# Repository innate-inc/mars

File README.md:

<div align="center">

<!-- Add your banner image here -->
<!--  -->

# Mars - A Personal AI Robot

*Complete design files and documentation for the Mars robot platform*

</div>

---

> [!WARNING]
> **This is an alpha release** - Breaking changes may occur. DIY builds are as-is without warranty.
> Purchase from us for guaranteed upgrades and full support.

---

## Philosophy

At Innate, we believe every builder should be a part of the robotics revolution, just like they were for the Personal Computer revolution.

To do so, two things are required: making robots **affordable**, but also **intuitive** and **powerful** to build with. MARS is our first platform and comes with every compute and sensor required for a general-purpose robot: navigation, manipulation, interaction with the best of AI.

With it, you can run (and build) VLAs, embodied agents, world models, and every other crazy idea you might have, for a BOM <$1k!

## Key Specifications

### Robotic Arm
- **Degrees of Freedom**: 5-DOF manipulator with modular end effector
- **Reach**: 10 inches (254mm) maximum
- **Payload**: 200g at full extension
- **Integrated Camera**: 150° field of view for vision-based manipulation

### Power
- **Battery Life**: ~5 hours with all systems running (navigation, manipulation, compute) using an 8000mAh battery*
  
*Battery delivered by Innate

For complete specifications, visit the [official documentation](https://docs.innate.bot).

## Repository Structure

This repository contains all the hardware design files you need to build a Mars robot:

### 📁 [Printed Parts](printed-parts/)
3D printable components including shells, layers, arm links, head, and mounting hardware. See the [printed-parts README](printed-parts/README.md) for details.

### 📁 [PCBs](pcbs/)
KiCad projects and production files for the head PCB and main development board. See the [pcbs README](pcbs/README.md) for details.

### Robot Models

[URDFs and bundled meshes](models/mars_description/README.md): the fixed-wheel
reference model and an experimental articulated-wheel physics variant, with
MuJoCo validation tests and documented calibration assumptions.

### 📄 Documentation
- **[Bill of Materials](BOM.md)** - Complete parts list with sourcing information
- **[Assembly Guide](assemblies.zip)** - Step-by-step assembly instructions

## Getting Started

1. **Review the [Bill of Materials](BOM.md)** - Source all required components
2. **Order PCBs** - See [pcbs/README.md](pcbs/README.md) for manufacturing instructions  
3. **3D Print Parts** - See [printed-parts/README.md](printed-parts/README.md) for printing guidelines
4. **Assemble** - Follow the instructions in [assemblies.zip](assemblies.zip)

## Contributing

We welcome contributions from the community! Feel free to:
- 🐛 Report bugs and issues
- 💡 Suggest new features and improvements
- 🔧 Submit pull requests
- 📖 Improve documentation

Please join our [Discord community](https://discord.gg/your-invite-link) to discuss your ideas before making major changes.

---

## 📜 License

This project uses dual licensing to cover hardware and software components:

### Hardware License: CERN-OHL-S-2.0

All hardware designs, PCB files, 3D models, and related documentation in this repository are licensed under the **CERN Open Hardware Licence Version 2 - Strongly Reciprocal** (CERN-OHL-S-2.0).

This is a copyleft license that ensures any modifications or derivative works must also be released under the same license, promoting open collaboration while protecting the open-source nature of the hardware.

📄 [View Hardware License](LICENSE-HARDWARE)  
🔗 [Learn more about CERN-OHL-S](https://ohwr.org/cern_ohl_s_v2.txt)

### Software License: GPL v3

The software components for this robot (to be released separately) are licensed under the **GNU General Public License v3.0** (GPL v3).

This ensures that any software modifications or derivative works remain open source and available to the community.

📄 [View Software License](LICENSE-SOFTWARE) *(Software repository coming soon)*  
🔗 [Learn more about GPL v3](https://www.gnu.org/licenses/gpl-3.0.en.html)

---

<div align="center">

**Built with 💙 by Innate in Palo Alto, California**

[Discord](https://discord.gg/your-invite-link) • [Documentation](https://docs.yoursite.com) • [Website](https://yourwebsite.com)

</div>

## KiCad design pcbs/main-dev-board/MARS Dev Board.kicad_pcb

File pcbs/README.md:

# PCBs

KiCad project files and production-ready outputs for all Mars robot circuit boards.

## 📋 Boards

### Head PCB
**Location**: `head-pcb/`

The head PCB controls sensors and actuators in the robot's head assembly.

- **KiCad Project**: [leader.kicad_pro](head-pcb/leader.kicad_pro)
- **Schematic**: [leader.kicad_sch](head-pcb/leader.kicad_sch)
- **PCB Layout**: [leader.kicad_pcb](head-pcb/leader.kicad_pcb)

**Production Files** (`head-pcb/production/`):
- [Gerbers & Drill Files](head-pcb/production/leader.zip)
- [BOM (Bill of Materials)](head-pcb/production/bom.csv)
- [Component Positions](head-pcb/production/positions.csv)
- [Designators Reference](head-pcb/production/designators.csv)
- [IPC Netlist](head-pcb/production/netlist.ipc)

### Main Development Board
**Location**: `main-dev-board/`

The main development board is the brain of the robot, handling computation and motor control."C:\Users\nick\Documents\Innate\mars\pcbs\main-dev-board\MARS%20Dev%20Board.kicad_pro"

- **KiCad Project**: [innate dev pcb.kicad_pro](main-dev-board/MARS%20Dev%20Board.kicad_pro)
- **Schematic**: [innate dev pcb.kicad_sch](main-dev-board/MARS%20Dev%20Board.kicad_sch)
- **PCB Layout**: [innate dev pcb.kicad_pcb](main-dev-board/MARS%20Dev%20Board.kicad_pcb)
- **3D Model**: [innate dev pcb.step](main-dev-board/MARS%20Dev%20Board.step)

**Production Files** (`main-dev-board/production/`):
- [Gerbers & Drill Files](main-dev-board/production/MARS_Dev_Board.zip)
- [BOM (Bill of Materials)](main-dev-board/production/bom.csv)
- [Component Positions](main-dev-board/production/positions.csv)
- [Designators Reference](main-dev-board/production/designators.csv)
- [IPC Netlist](main-dev-board/production/netlist.ipc)

## Design Modifications

To modify the PCB designs:
1. Install [KiCad 7.0+](https://www.kicad.org/)
2. Open the `.kicad_pro` file in KiCad
3. Make your changes to schematic and/or layout
4. Regenerate production files using KiCad's fabrication output tools

## 📐 Fabrication Toolkit

Both boards include `fabrication-toolkit-options.json` for automated production file generation.

## ⚡ Important Notes

- Always verify board revisions match your BOM
- Double-check component orientations before assembly
- Test boards thoroughly before integration
- Refer to the [main BOM](../BOM.md) for complete sourcing information

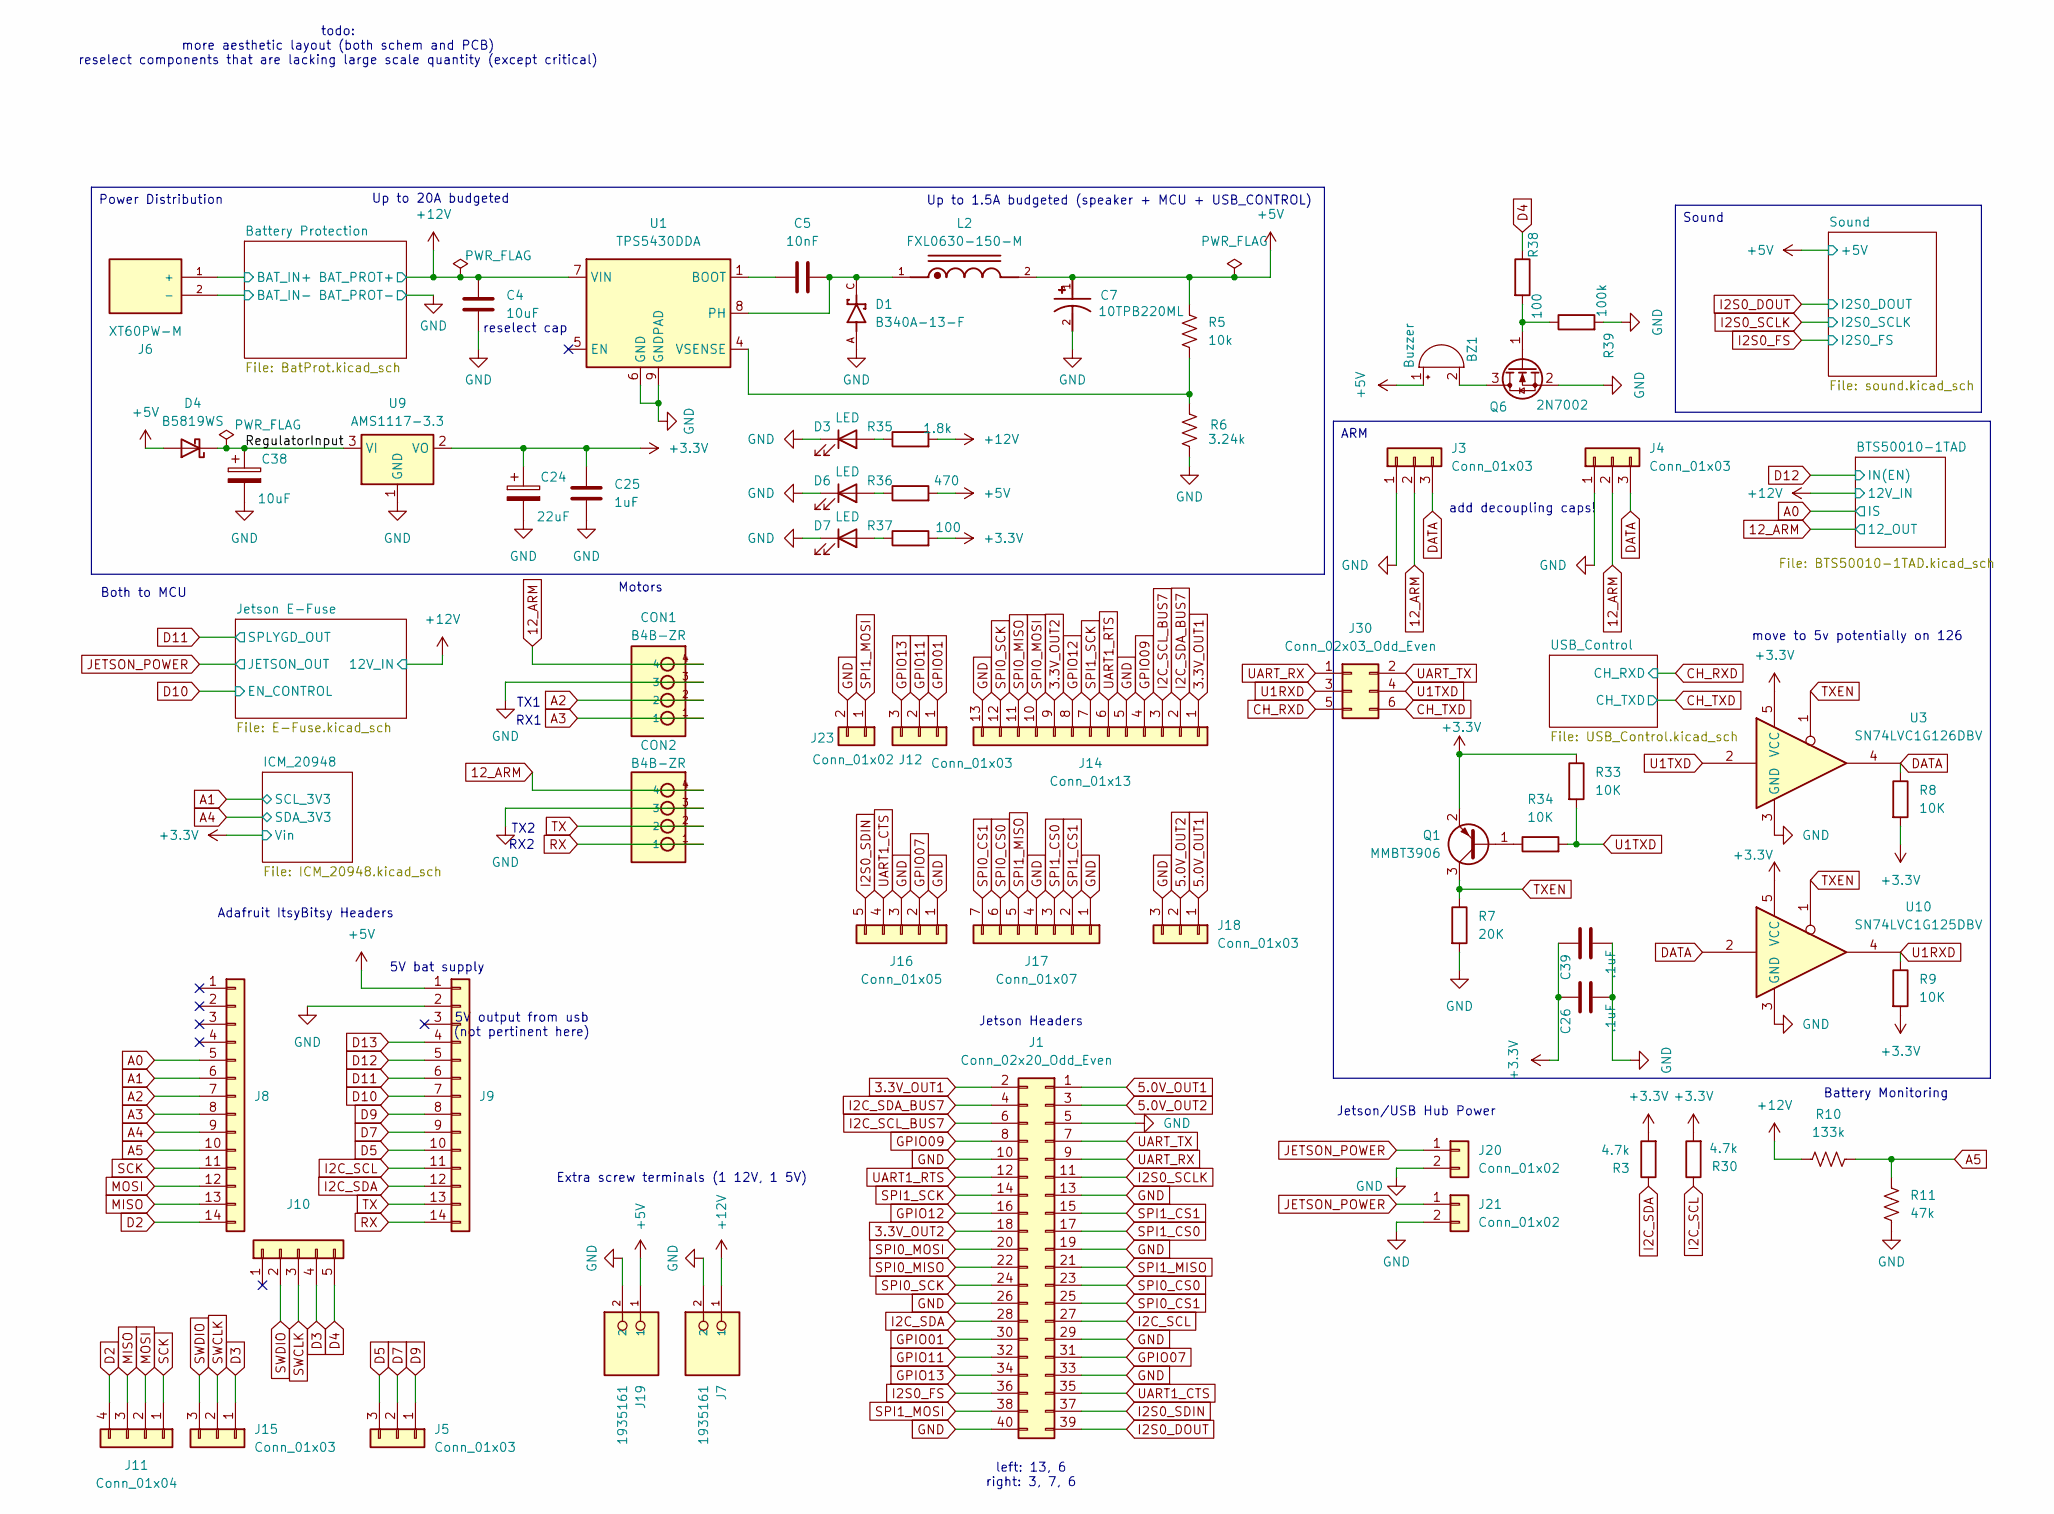
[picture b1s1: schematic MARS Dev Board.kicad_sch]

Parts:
BZ1: Buzzer; XDCR_KXG1205C; LCSC Part # C1122355
C4: 10uF; C_0805_2012Metric; LCSC Part # C3039694
C5: 10nF; C_0603_1608Metric; LCSC Part # C1691
C7: 10TPB220ML; CAP_10TPB220ML; PARTREV 30-Nov-20; LCSC Part # C347545
C24: 22uF; CAPMP3516X190N; LCSC Part # C2158664
C25: 1uF; C_0603_1608Metric; LCSC Part # C29936
C26, C39: .1uF; C_0402_1005Metric; LCSC Part # C56392
C38: 10uF; CAPMP3516X190N; LCSC Part # C7194
CON1, CON2: B4B-ZR; LCSC Part # C157997
D1: B340A-13-F; DIOM5226X240N; PARTREV 17-2; LCSC Part # C908680
D3, D6, D7: LED; D_0603_1608Metric; LCSC Part # C12065
D4: B5819WS; D_SOD-323; LCSC Part # C22624
J1: Conn_02x20_Odd_Even; PinSocket_2x20_P2.54mm_Vertical; LCSC Part # C2682225
J3, J4: Conn_01x03; JST_EH_B3B-EH-A_1x03_P2.50mm_Vertical; LCSC Part # C398546
J5, J12, J15, J18: Conn_01x03; PinSocket_1x03_P2.54mm_Vertical; LCSC Part # C146243
J6: XT60PW-M; AMASS_XT60PW-M; PARTREV V1.2; LCSC Part # C98732
J7, J19: 1935161; TerminalBlock_Phoenix_PT-1,5-2-5.0-H_1x02_P5.00mm_Horizontal; PARTREV 14.12.2022; LCSC Part # C8404
J8, J9: Conn_01x14; PinSocket_1x14_P2.54mm_Vertical; LCSC Part # C18078135
J10, J16: Conn_01x05; PinSocket_1x05_P2.54mm_Vertical; LCSC Part # C18078128
J11: Conn_01x04; PinSocket_1x04_P2.54mm_Vertical; LCSC Part # C7499324
J14: Conn_01x13; PinSocket_1x13_P2.54mm_Vertical; LCSC Part # C2685211
J17: Conn_01x07; PinSocket_1x07_P2.54mm_Vertical; LCSC Part # C18078130
J20, J21: Conn_01x02; JST_VH_B2P-VH_1x02_P3.96mm_Vertical; LCSC Part # C160315
J23: Conn_01x02; PinSocket_1x02_P2.54mm_Vertical; LCSC Part # C18078125
J30: Conn_02x03_Odd_Even; PinHeader_2x03_P2.54mm_Vertical; LCSC Part # C124384
L2: FXL0630-150-M; INDM7066X300N; PARTREV A; LCSC Part # C177243
Q1: MMBT3906; SOT-23; LCSC Part # C53444
Q6: 2N7002; SOT-23; LCSC Part # C8545
R3, R30: 4.7k; R_0402_1005Metric; LCSC Part # C25900
R5: 10k; R_0603_1608Metric; LCSC Part # C15401
R6: 3.24k; R_0603_1608Metric; LCSC Part # C22994
R7: 20K; R_0402_1005Metric; LCSC Part # C25765
R8, R9, R33, R34: 10K; R_0402_1005Metric; LCSC Part # C25744
R10: 133k; R_0402_1005Metric; LCSC Part # C25753
R11: 47k; R_0402_1005Metric; LCSC Part # C25792
R35: 1.8k; R_0402_1005Metric; LCSC Part # C25932
R36: 470; R_0402_1005Metric; LCSC Part # C25167
R37, R38: 100; R_0402_1005Metric; LCSC Part # C25076
R39: 100k; R_0402_1005Metric; LCSC Part # C25741
U1: TPS5430DDA; TI_SO-PowerPAD-8_ThermalVias; LCSC Part # C9864
U3: SN74LVC1G126DBV; SOT-23-5; LCSC Part # C7834
U9: AMS1117-3.3; SOT-223-3_TabPin2; LCSC Part # C347222
U10: SN74LVC1G125DBV; SOT-23-5; LCSC Part # C23654

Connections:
3.3V_OUT1: J1.2, J14.1
3.3V_OUT2: J1.18, J14.9
5.0V_OUT1: J1.1, J18.1
5.0V_OUT2: J1.3, J18.2
12_ARM: CON1.4, CON2.4, J3.2, J4.2; also elsewhere on the board
+3.3V: C24.1, C25.1, C26.1, C39.1, Q1.2 (E), R3.2, R8.2, R9.2, R30.2, R33.1, R37.2, U3.5 (VCC), U9.2 (VO), U10.5 (VCC); also elsewhere on the board
+5V: BZ1.1 (+), C7.1, D4.2 (A), J9.1, J19.1, L2.2, R5.1, R36.2; also elsewhere on the board
+12V: C4.1, J7.1, R10.1, R35.2, U1.7 (VIN); also elsewhere on the board
/Battery Protection/BAT_IN+: J6.1 (+); also elsewhere on the board
/RegulatorInput: C38.1, D4.1 (K), U9.3 (VI)
A0: J8.5; also elsewhere on the board
A1: J8.6; also elsewhere on the board
A2: CON1.2, J8.7
A3: CON1.1, J8.8
A4: J8.9; also elsewhere on the board
A5: J8.10, R10.2, R11.1
CH_RXD: J30.5; also elsewhere on the board
CH_TXD: J30.6; also elsewhere on the board
D2: J8.14, J11.4
D3: J10.4, J15.1
D4: J10.5, R38.1
D5: J5.3, J9.10
D7: J5.2, J9.9
D9: J5.1, J9.8
D10: J9.7; also elsewhere on the board
D11: J9.6; also elsewhere on the board
D12: J9.5; also elsewhere on the board
D13: J9.4
DATA: J3.3, J4.3, R8.1, U3.4, U10.2
GND: C4.2, C7.2, C24.2, C25.2, C26.2, C38.2, C39.2, CON1.3, CON2.3, D1.A, D3.1 (K), D6.1 (K), D7.1 (K), J1.5, J1.10, J1.13, J1.19, J1.26, J1.29, J1.33, J1.40, J3.1, J4.1, J6.2 (-), J7.2, J9.2, J14.5, J14.13, J16.1, J16.3, J17.1, J17.4, J18.3, J19.2, J20.2, J21.2, J23.2, Q6.2 (S), R6.2, R7.2, R11.2, R39.2, U1.6 (GND), U1.9 (GNDPAD), U3.3 (GND), U9.1 (GND), U10.3 (GND); also elsewhere on the board
GPIO01: J1.30, J12.1
GPIO07: J1.31, J16.2
GPIO09: J1.8, J14.4
GPIO11: J1.32, J12.2
GPIO12: J1.16, J14.8
GPIO13: J1.34, J12.3
I2C_SCL: J1.27, J9.11, R30.1
I2C_SCL_BUS7: J1.6, J14.3
I2C_SDA: J1.28, J9.12, R3.1
I2C_SDA_BUS7: J1.4, J14.2
I2S0_DOUT: J1.39; also elsewhere on the board
I2S0_FS: J1.36; also elsewhere on the board
I2S0_SCLK: J1.11; also elsewhere on the board
I2S0_SDIN: J1.37, J16.5
JETSON_POWER: J20.1, J21.1; also elsewhere on the board
MISO: J8.13, J11.3
MOSI: J8.12, J11.2
unnamed: BZ1.2 (-), Q6.3 (D)
unnamed: D3.2 (A), R35.1
unnamed: D6.2 (A), R36.1
unnamed: D7.2 (A), R37.1
unnamed: Q1.1 (B), R34.1
unnamed: Q6.1 (G), R38.2, R39.1
unnamed: C5.1, U1.1 (BOOT)
unnamed: C5.2, D1.C, L2.1, U1.8 (PH)
unnamed: R5.2, R6.1, U1.4 (VSENSE)
RX: CON2.1, J9.14
SCK: J8.11, J11.1
SPI0_CS0: J1.23, J17.6
SPI0_CS1: J1.25, J17.7
SPI0_MISO: J1.22, J14.11
SPI0_MOSI: J1.20, J14.10
SPI0_SCK: J1.24, J14.12
SPI1_CS0: J1.17, J17.3
SPI1_CS1: J1.15, J17.2
SPI1_MISO: J1.21, J17.5
SPI1_MOSI: J1.38, J23.1
SPI1_SCK: J1.14, J14.7
SWCLK: J10.3, J15.2
SWDIO: J10.2, J15.3
TX: CON2.2, J9.13
TXEN: Q1.3 (C), R7.1, U3.1, U10.1
U1RXD: J30.3, R9.1, U10.4
U1TXD: J30.4, R33.2, R34.2, U3.2
UART1_CTS: J1.35, J16.4
UART1_RTS: J1.12, J14.6
UART_RX: J1.9, J30.1
UART_TX: J1.7, J30.2

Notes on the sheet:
Adafruit ItsyBitsy Headers
Battery Monitoring
Up to 20A budgeted
Both to MCU
5V output from usb (not pertinent here)
Extra screw terminals (1 12V, 1 5V)
Jetson/USB Hub Power
RX2
5V bat supply
TX1
add decoupling caps!
Jetson Headers
left: 13, 6 right: 3, 7, 6
TX2
reselect cap
RX1
Motors
move to 5v potentially on 126
Up to 1.5A budgeted (speaker + MCU + USB_CONTROL)
todo: more aesthetic layout (both schem and PCB) reselect components that are lacking large scale quantity (except critical)
Power Distribution
Sound
ARM

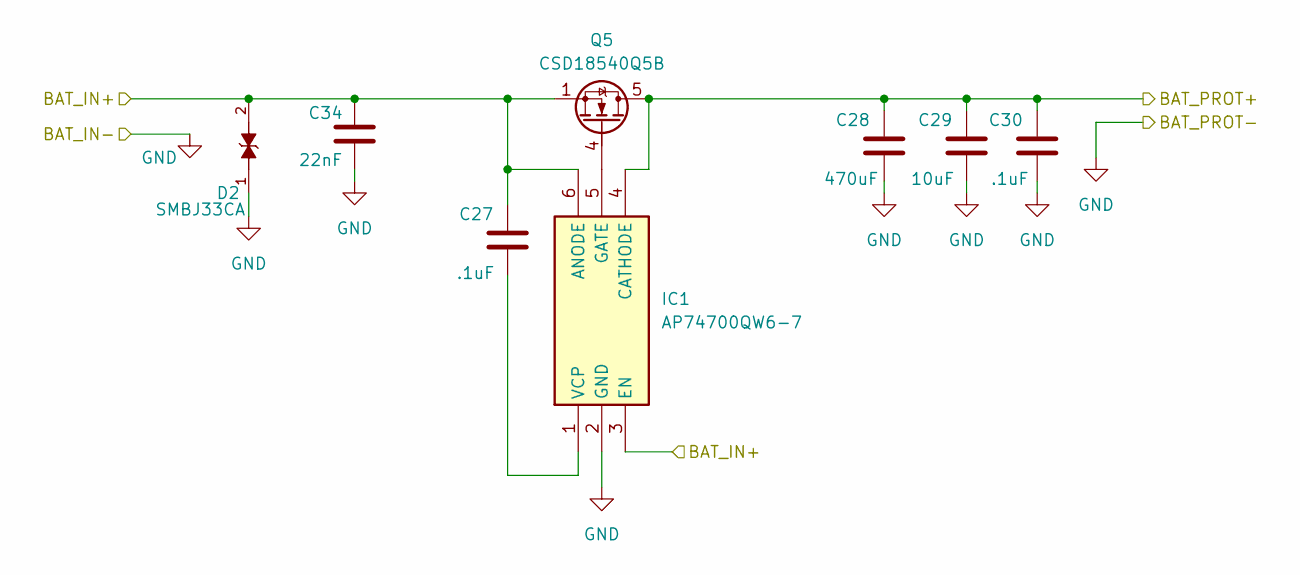
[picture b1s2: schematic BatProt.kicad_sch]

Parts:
C27, C30: .1uF; C_0402_1005Metric; LCSC Part # C56392
C28: 470uF; C_Elec_10x10.2; LCSC Part # C242138
C29: 10uF; C_0805_2012Metric; LCSC Part # C3039694
C34: 22nF; C_0402_1005Metric; LCSC Part # C76703
D2: SMBJ33CA; DIOM4336X265N; PARTREV I2102; LCSC Part # C78420
IC1: AP74700QW6-7; SOT95P280X145-6N; Manufacturer_Part_Number AP74700QW6-7; Mouser Part Number 621-AP74700QW6-7
Q5: CSD18540Q5B; TDSON-8-1; LCSC Part # C86513

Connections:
+12V: C28.1, C29.1, C30.1, IC1.4 (CATHODE), Q5.5 (D); also elsewhere on the board
/Battery Protection/BAT_IN+: C27.1, C34.1, D2.2, IC1.3 (EN), IC1.6 (ANODE), Q5.1 (S), Q5.2 (S), Q5.3 (S); also elsewhere on the board
GND: C28.2, C29.2, C30.2, C34.2, D2.1, IC1.2 (GND); also elsewhere on the board
unnamed: IC1.5 (GATE), Q5.4 (G)
unnamed: C27.2, IC1.1 (VCP)

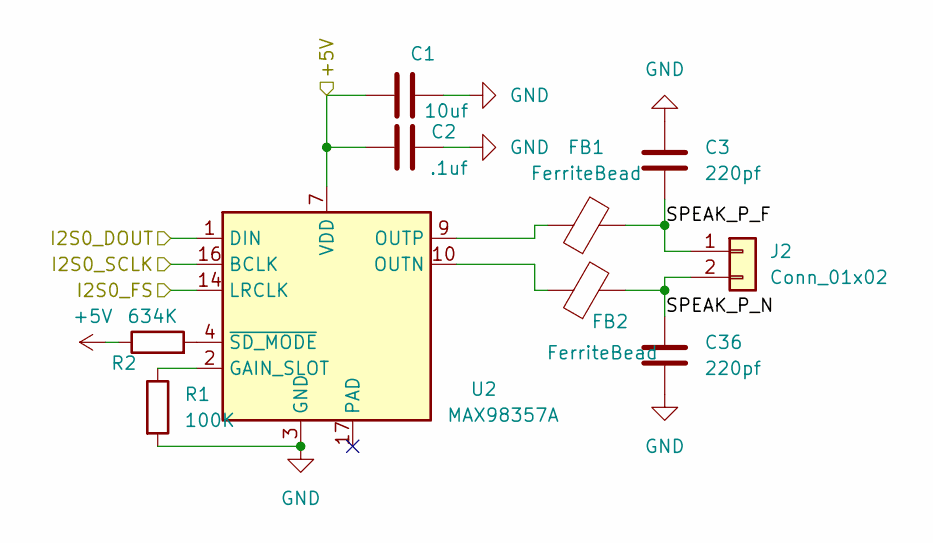
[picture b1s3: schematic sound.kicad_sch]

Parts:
C1: 10uf; C_0603_1608Metric; LCSC Part # C19702
C2: .1uf; C_0402_1005Metric; LCSC Part # C56392
C3, C36: 220pf; C_0402_1005Metric; LCSC Part # C117751
FB1, FB2: FerriteBead; C_0402_1005Metric_Pad0.74x0.62mm_HandSolder; LCSC Part # C85817
J2: Conn_01x02; JST_XH_B2B-XH-A_1x02_P2.50mm_Vertical; LCSC Part # C158012
R1: 100K; R_0402_1005Metric; LCSC Part # C25741
R2: 634K; R_0402_1005Metric; LCSC Part # C270588
U2: MAX98357A; TQFN-16-1EP_3x3mm_P0.5mm_EP1.23x1.23mm; LCSC Part # C910544

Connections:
+5V: C1.1, C2.1, R2.1, U2.7 (VDD), U2.8 (VDD); also elsewhere on the board
/Sound/SPEAK_P_F: C3.2, FB1.2, J2.1
/Sound/SPEAK_P_N: C36.1, FB2.2, J2.2
GND: C1.2, C2.2, C3.1, C36.2, R1.2, U2.3 (GND), U2.11 (GND), U2.15 (GND); also elsewhere on the board
I2S0_DOUT: U2.1 (DIN); also elsewhere on the board
I2S0_FS: U2.14 (LRCLK); also elsewhere on the board
I2S0_SCLK: U2.16 (BCLK); also elsewhere on the board
unnamed: R1.1, U2.2 (GAIN_SLOT)
unnamed: FB2.1, U2.10 (OUTN)
unnamed: FB1.1, U2.9 (OUTP)
unnamed: R2.2, U2.4 (~SD_MODE)

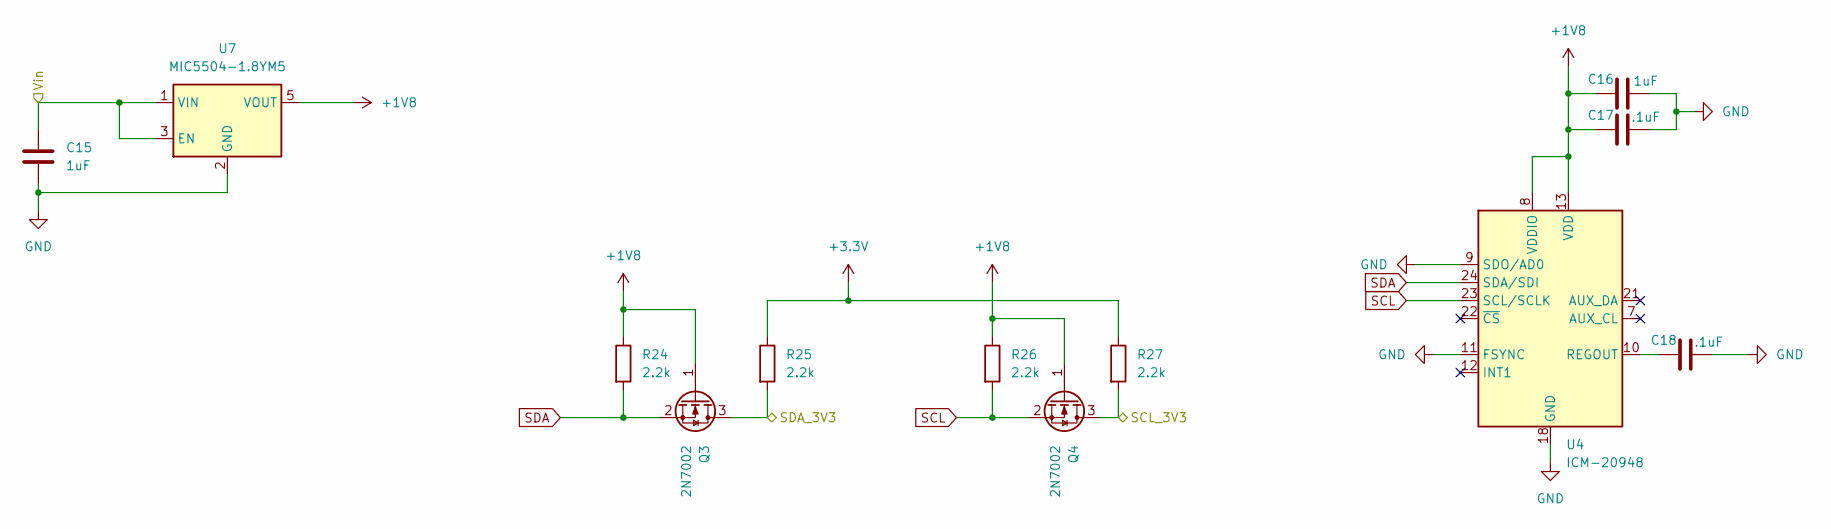
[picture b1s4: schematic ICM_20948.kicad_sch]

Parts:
C15, C16: 1uF; C_0603_1608Metric; LCSC Part # C29936
C17, C18: .1uF; C_0402_1005Metric; LCSC Part # C56392
Q3, Q4: 2N7002; SOT-23; LCSC Part # C8545
R24, R25, R26, R27: 2.2k; R_0402_1005Metric; LCSC Part # C25879
U4: ICM-20948; InvenSense_QFN-24_3x3mm_P0.4mm; LCSC Part # C726001
U7: MIC5504-1.8YM5; SOT-23-5; LCSC Part # C3040643

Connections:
+1V8: C16.1, C17.1, Q3.1 (G), Q4.1 (G), R24.1, R26.1, U4.8 (VDDIO), U4.13 (VDD), U7.5 (VOUT)
+3.3V: C15.1, R25.1, R27.1, U7.1 (VIN), U7.3 (EN); also elsewhere on the board
A1: Q4.3 (D), R27.2; also elsewhere on the board
A4: Q3.3 (D), R25.2; also elsewhere on the board
GND: C15.2, C16.2, C17.2, C18.2, U4.9 (SDO/AD0), U4.11 (FSYNC), U4.18 (GND), U4.20 (GND), U7.2 (GND); also elsewhere on the board
unnamed: C18.1, U4.10 (REGOUT)
SCL: Q4.2 (S), R26.2, U4.23 (SCL/SCLK)
SDA: Q3.2 (S), R24.2, U4.24 (SDA/SDI)

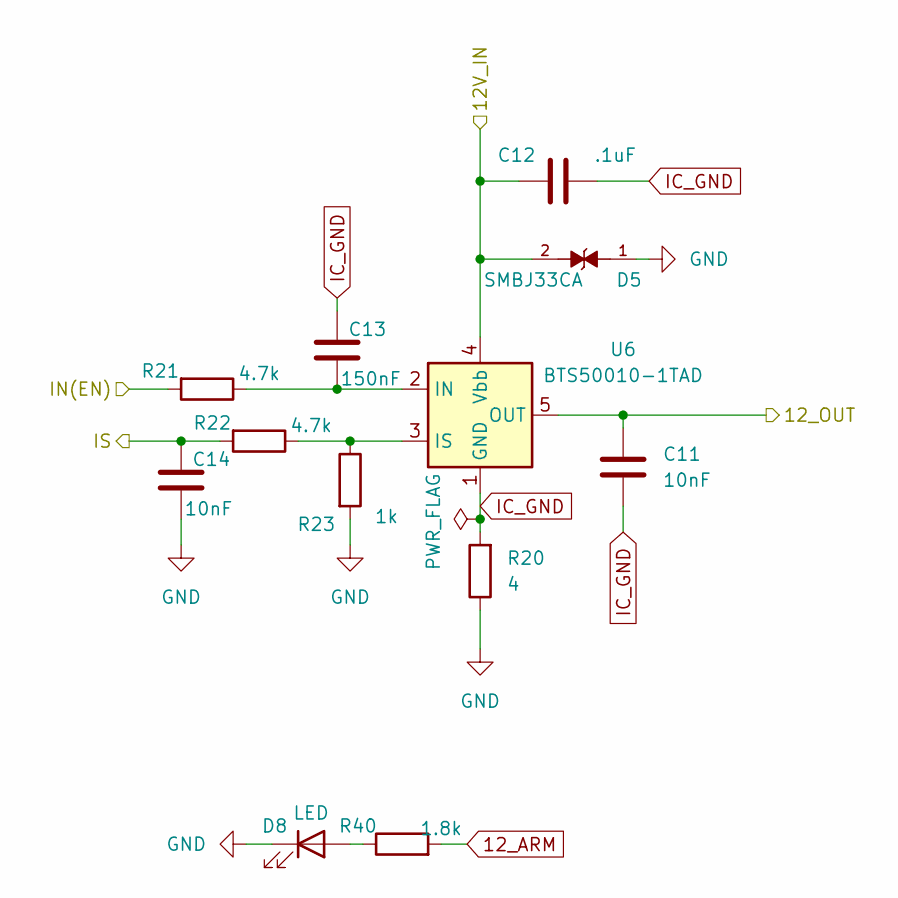
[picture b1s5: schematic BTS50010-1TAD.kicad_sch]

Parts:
C11, C14: 10nF; C_0402_1005Metric; LCSC Part # C76702
C12: .1uF; C_0402_1005Metric; LCSC Part # C56392
C13: 150nF; C_0402_1005Metric; LCSC Part # C5448879
D5: SMBJ33CA; DIOM4336X265N; PARTREV I2102; LCSC Part # C78420
D8: LED; D_0603_1608Metric; LCSC Part # C12065
R20: 4; R_0402_1005Metric; LCSC Part # C270603
R21, R22: 4.7k; R_0402_1005Metric; LCSC Part # C25900
R23: 1k; R_0402_1005Metric; LCSC Part # C11702
R40: 1.8k; R_0402_1005Metric; LCSC Part # C25932
U6: BTS50010-1TAD; TO-263-7_TabPin4; LCSC Part # C2150443

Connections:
12_ARM: C11.1, R40.2, U6.5 (OUT), U6.6 (OUT), U6.7 (OUT); also elsewhere on the board
+12V: C12.1, D5.2, U6.4 (Vbb); also elsewhere on the board
A0: C14.1, R22.2; also elsewhere on the board
D12: R21.2; also elsewhere on the board
GND: C14.2, D5.1, D8.1 (K), R20.1, R23.2; also elsewhere on the board
IC_GND: C11.2, C12.2, C13.1, R20.2, U6.1 (GND)
unnamed: D8.2 (A), R40.1
unnamed: C13.2, R21.1, U6.2 (IN)
unnamed: R22.1, R23.1, U6.3 (IS)

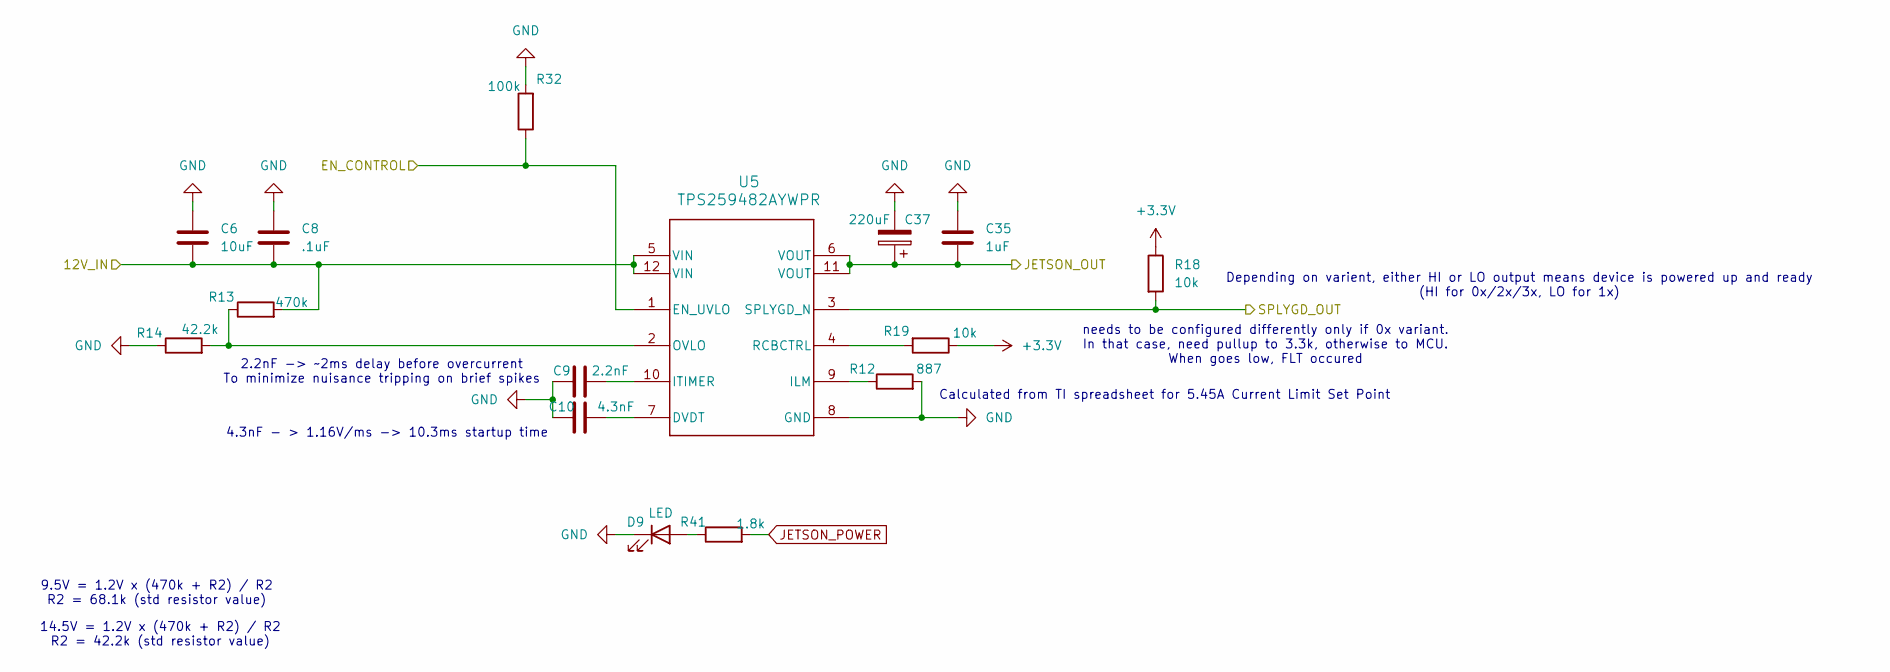
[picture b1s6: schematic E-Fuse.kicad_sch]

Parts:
C6: 10uF; C_0805_2012Metric; LCSC Part # C3039694
C8: .1uF; C_0402_1005Metric; LCSC Part # C56392
C9: 2.2nF; C_0402_1005Metric; LCSC Part # C541386
C10: 4.3nF; C_0402_1005Metric; LCSC Part # C181747
C35: 1uF; C_0603_1608Metric; LCSC Part # C29936
C37: 220uF; C_Elec_8x10.2; LCSC Part # C341198
D9: LED; D_0603_1608Metric; LCSC Part # C12065
R12: 887; R_0402_1005Metric; LCSC Part # C474137
R13: 470k; R_0402_1005Metric; LCSC Part # C25790
R14: 42.2k; R_0402_1005Metric; LCSC Part # C26979
R18, R19: 10k; R_0402_1005Metric; LCSC Part # C25744
R32: 100k; R_0402_1005Metric; LCSC Part # C25741
R41: 1.8k; R_0402_1005Metric; LCSC Part # C25932
U5: TPS259482AYWPR; YWP0012A-MFG; LCSC Part # C22422005

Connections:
+3.3V: R18.1, R19.1; also elsewhere on the board
+12V: C6.2, C8.2, R13.2, U5.5 (VIN), U5.12 (VIN); also elsewhere on the board
D10: R32.1, U5.1 (EN_UVLO); also elsewhere on the board
D11: R18.2, U5.3 (SPLYGD_N); also elsewhere on the board
GND: C6.1, C8.1, C9.1, C10.1, C35.1, C37.2, D9.1 (K), R12.2, R14.1, R32.2, U5.8 (GND); also elsewhere on the board
JETSON_POWER: C35.2, C37.1, R41.2, U5.6 (VOUT), U5.11 (VOUT); also elsewhere on the board
unnamed: D9.2 (A), R41.1
unnamed: C10.2, U5.7 (DVDT)
unnamed: R12.1, U5.9 (ILM)
unnamed: C9.2, U5.10 (ITIMER)
unnamed: R13.1, R14.2, U5.2 (OVLO)
unnamed: R19.2, U5.4 (RCBCTRL)

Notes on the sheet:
14.5V = 1.2V x (470k + R2) / R2 R2 = 42.2k (std resistor value)
Calculated from TI spreadsheet for 5.45A Current Limit Set Point
Depending on varient, either HI or LO output means device is powered up and ready (HI for 0x/2x/3x, LO for 1x)
2.2nF -> ~2ms delay before overcurrent To minimize nuisance tripping on brief spikes
9.5V = 1.2V x (470k + R2) / R2 R2 = 68.1k (std resistor value)
4.3nF - > 1.16V/ms -> 10.3ms startup time
needs to be configured differently only if 0x variant. In that case, need pullup to 3.3k, otherwise to MCU. When goes low, FLT occured

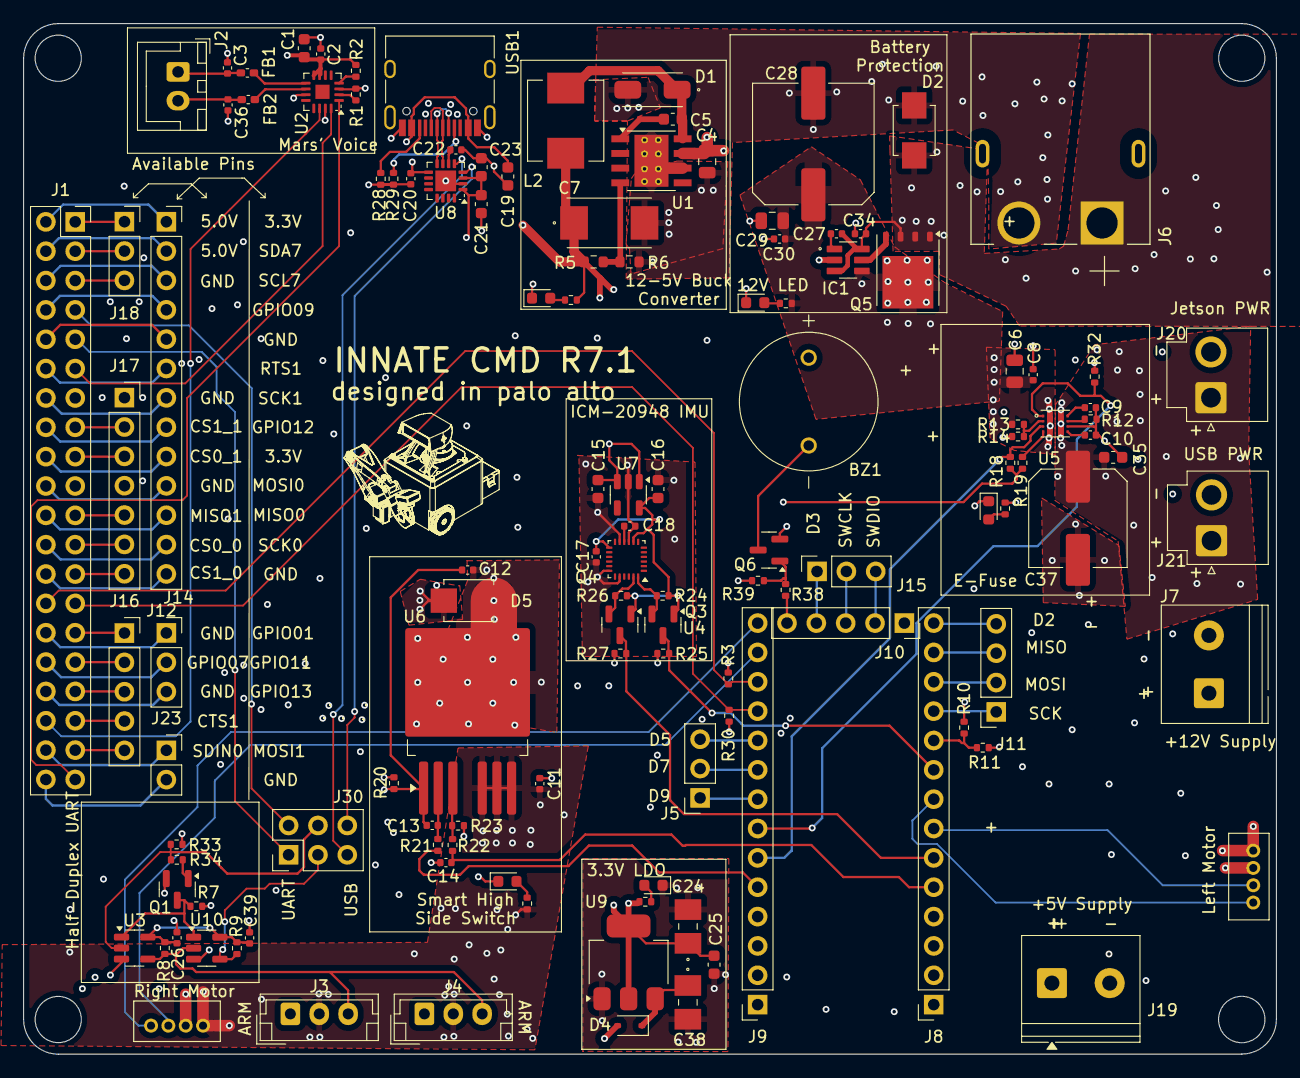
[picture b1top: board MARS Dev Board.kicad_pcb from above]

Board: 6 copper layers, 108.4 x 89.2 mm, 126 parts (0 on the bottom side), 105 nets.

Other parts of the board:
C19: 10uF; C_0603_1608Metric
C20, C22: .1uF; C_0402_1005Metric
C21, C23: 1uF; C_0603_1608Metric
R28, R29: 5k1; R_0402_1005Metric
U8: CH343P; WCH_QFN-16-1EP_3x3mm_P0.5mm_EP1.8x1.8mm
USB1: USB_C_Receptacle_HRO_TYPE-C-31-M-12

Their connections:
+3.3V: C21.2, C23.2, U8.1 (VIO), U8.3 (VDD5); also elsewhere on the board
/USB_Control/3v3_OP: C22.2, U8.6 (V3_{OUT})
/USB_Control/CC1: R29.1, USB1.A5 (CC1)
/USB_Control/CC2: R28.1, USB1.B5 (CC2)
/USB_Control/USBD_N: U8.8 (UD-), USB1.A7 (DN1), USB1.B7 (DN2)
/USB_Control/USBD_P: U8.7 (UD+), USB1.A6 (DP1), USB1.B6 (DP2)
CH_RXD: U8.5 (RXD); also elsewhere on the board
CH_TXD: U8.4 (TXD); also elsewhere on the board
GND: C19.1, C20.1, C21.1, C22.1, C23.1, R28.2, R29.2, U8.2 (GND), U8.17 (GND_EPAD), USB1.A1B12 (GND), USB1.B1A12 (GND); also elsewhere on the board
VDDUSB: C19.2, C20.2, U8.9 (VBUS), USB1.A4B9 (VBUS), USB1.B4A9 (VBUS)

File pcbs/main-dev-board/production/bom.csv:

"Reference","Value","DNP","Exclude from BOM","Exclude from Board","Footprint","LCSC Part #"
"D2,D5","SMBJ33CA","","","","SMBJ33CA:DIOM4336X265N","C78420"
"J7,J19","1935161","","","","TerminalBlock_Phoenix:TerminalBlock_Phoenix_PT-1,5-2-5.0-H_1x02_P5.00mm_Horizontal","C8404"
"C7","10TPB220ML","","","","10TPB220ML:CAP_10TPB220ML","C347545"
"L2","FXL0630-150-M","","","","FXL0630-150-M:INDM7066X300N","C177243"
"D1","B340A-13-F","","","","B340A-13-F:DIOM5226X240N","C908680"
"J6","XT60PW-M","","","","AMASS_XT60PW-M:AMASS_XT60PW-M","C98732"
"USB1","~","","","","Connector_USB:USB_C_Receptacle_HRO_TYPE-C-31-M-12","C165948"
"U10","SN74LVC1G125DBV","","","","Package_TO_SOT_SMD:SOT-23-5","C23654"
"U9","AMS1117-3.3","","","","Package_TO_SOT_SMD:SOT-223-3_TabPin2","C347222"
"U8","CH343P","","","","Package_DFN_QFN:WCH_QFN-16-1EP_3x3mm_P0.5mm_EP1.8x1.8mm","C2846043"
"U7","MIC5504-1.8YM5","","","","Package_TO_SOT_SMD:SOT-23-5","C3040643"
"U6","BTS50010-1TAD","","","","Package_TO_SOT_SMD:TO-263-7_TabPin4","C2150443"
"U5","TPS259482AYWPR","","","","tps25948:YWP0012A-MFG","C22422005"
"U4","ICM-20948","","","","Sensor_Motion:InvenSense_QFN-24_3x3mm_P0.4mm"," C726001"
"U3","SN74LVC1G126DBV","","","","Package_TO_SOT_SMD:SOT-23-5"," C7834"
"U2","MAX98357A","","","","Package_DFN_QFN:TQFN-16-1EP_3x3mm_P0.5mm_EP1.23x1.23mm","C910544"
"U1","TPS5430DDA","","","","Package_SO:TI_SO-PowerPAD-8_ThermalVias","C9864"
"R37,R38","100","","","","Resistor_SMD:R_0402_1005Metric","C25076"
"R36","470","","","","Resistor_SMD:R_0402_1005Metric","C25167"
"R35,R40,R41","1.8k","","","","Resistor_SMD:R_0402_1005Metric","C25932"
"R32,R39","100k","","","","Resistor_SMD:R_0402_1005Metric","C25741"
"R28,R29","5k1","","","","Resistor_SMD:R_0402_1005Metric","C25905"
"R24,R25,R26,R27","2.2k","","","","Resistor_SMD:R_0402_1005Metric","C25879"
"R23","1k","","","","Resistor_SMD:R_0402_1005Metric","C11702"
"R20","4","","","","Resistor_SMD:R_0402_1005Metric","C270603"
"R18,R19","10k","","","","Resistor_SMD:R_0402_1005Metric","C25744"
"R14","42.2k","","","","Resistor_SMD:R_0402_1005Metric","C26979"
"R13","470k","","","","Resistor_SMD:R_0402_1005Metric","C25790"
"R12","887","","","","Resistor_SMD:R_0402_1005Metric","C474137"
"R11","47k","","","","Resistor_SMD:R_0402_1005Metric","C25792"
"R10","133k","","","","Resistor_SMD:R_0402_1005Metric"," C25753"
"R8,R9,R33,R34","10K","","","","Resistor_SMD:R_0402_1005Metric","C25744"
"R7","20K","","","","Resistor_SMD:R_0402_1005Metric","C25765"
"R6","3.24k","","","","Resistor_SMD:R_0603_1608Metric","C22994"
"R5","10k","","","","Resistor_SMD:R_0603_1608Metric","C15401"
"R3,R21,R22,R30","4.7k","","","","Resistor_SMD:R_0402_1005Metric","C25900"
"R2","634K","","","","Resistor_SMD:R_0402_1005Metric","C270588"
"R1","100K","","","","Resistor_SMD:R_0402_1005Metric","C25741"
"Q5","CSD18540Q5B","","","","Package_TO_SOT_SMD:TDSON-8-1"," C86513"
"Q3,Q4,Q6","2N7002","","","","Package_TO_SOT_SMD:SOT-23","C8545"
"Q1","MMBT3906","","","","Package_TO_SOT_SMD:SOT-23","C53444"
"J30","Conn_02x03_Odd_Even","","","","Connector_PinHeader_2.54mm:PinHeader_2x03_P2.54mm_Vertical","C124384"
"J23","Conn_01x02","","","","Connector_PinSocket_2.54mm:PinSocket_1x02_P2.54mm_Vertical","C18078125"
"J20,J21","Conn_01x02","","","","Connector_JST:JST_VH_B2P-VH_1x02_P3.96mm_Vertical","C160315"
"J17","Conn_01x07","","","","Connector_PinSocket_2.54mm:PinSocket_1x07_P2.54mm_Vertical","C18078130"
"J14","Conn_01x13","","","","Connector_PinSocket_2.54mm:PinSocket_1x13_P2.54mm_Vertical","C2685211"
"J11","Conn_01x04","","","","Connector_PinSocket_2.54mm:PinSocket_1x04_P2.54mm_Vertical","C7499324"
"J10,J16","Conn_01x05","","","","Connector_PinSocket_2.54mm:PinSocket_1x05_P2.54mm_Vertical","C18078128"
"J8,J9","Conn_01x14","","","","Connector_PinSocket_2.54mm:PinSocket_1x14_P2.54mm_Vertical","C18078135"
"J5,J12,J15,J18","Conn_01x03","","","","Connector_PinSocket_2.54mm:PinSocket_1x03_P2.54mm_Vertical","C146243"
"J3,J4","Conn_01x03","","","","Connector_JST:JST_EH_B3B-EH-A_1x03_P2.50mm_Vertical","C398546"
"J2","Conn_01x02","","","","Connector_JST:JST_XH_B2B-XH-A_1x02_P2.50mm_Vertical","C158012"
"J1","Conn_02x20_Odd_Even","","","","Connector_PinSocket_2.54mm:PinSocket_2x20_P2.54mm_Vertical","C2682225"
"IC1","AP74700QW6-7","","","","SOT-26:SOT95P280X145-6N","C5381661"
"FB1,FB2","FerriteBead","","","","Capacitor_SMD:C_0402_1005Metric_Pad0.74x0.62mm_HandSolder","C85817"
"D4","B5819WS","","","","Diode_SMD:D_SOD-323","C22624"
"D3,D6,D7,D8,D9","LED","","","","Diode_SMD:D_0603_1608Metric","C12065"
"CON1,CON2","B4B-ZR","","","","B4B-ZR:B4B-ZR","C157997"
"C38","10uF","","","","10uFTant:CAPMP3516X190N","C7194"
"C37","220uF","","","","Capacitor_SMD:C_Elec_8x10.2","C341198"
"C34","22nF","","","","Capacitor_SMD:C_0402_1005Metric","C76703"
"C28","470uF","","","","Capacitor_SMD:C_Elec_10x10.2"," C242138"
"C24","22uF","","","","10uFTant:CAPMP3516X190N","C2158664"
"C19","10uF","","","","Capacitor_SMD:C_0603_1608Metric","C19702"
"C15,C16,C21,C23,C25,C35","1uF","","","","Capacitor_SMD:C_0603_1608Metric","C29936"
"C13","150nF","","","","Capacitor_SMD:C_0402_1005Metric","C5448879"
"C11,C14","10nF","","","","Capacitor_SMD:C_0402_1005Metric","C76702"
"C10","4.3nF","","","","Capacitor_SMD:C_0402_1005Metric","C181747"
"C9","2.2nF","","","","Capacitor_SMD:C_0402_1005Metric","C541386"
"C8,C12,C17,C18,C20,C22,C26,C27,C30,C39",".1uF","","","","Capacitor_SMD:C_0402_1005Metric","C56392"
"C5","10nF","","","","Capacitor_SMD:C_0603_1608Metric","C1691"
"C4,C6,C29","10uF","","","","Capacitor_SMD:C_0805_2012Metric","C3039694"
"C3,C36","220pf","","","","Capacitor_SMD:C_0402_1005Metric","C117751"
"C2",".1uf","","","","Capacitor_SMD:C_0402_1005Metric","C56392"
"C1","10uf","","","","Capacitor_SMD:C_0603_1608Metric","C19702"
"BZ1","Buzzer","","","","Buzzer:XDCR_KXG1205C","C1122355"
